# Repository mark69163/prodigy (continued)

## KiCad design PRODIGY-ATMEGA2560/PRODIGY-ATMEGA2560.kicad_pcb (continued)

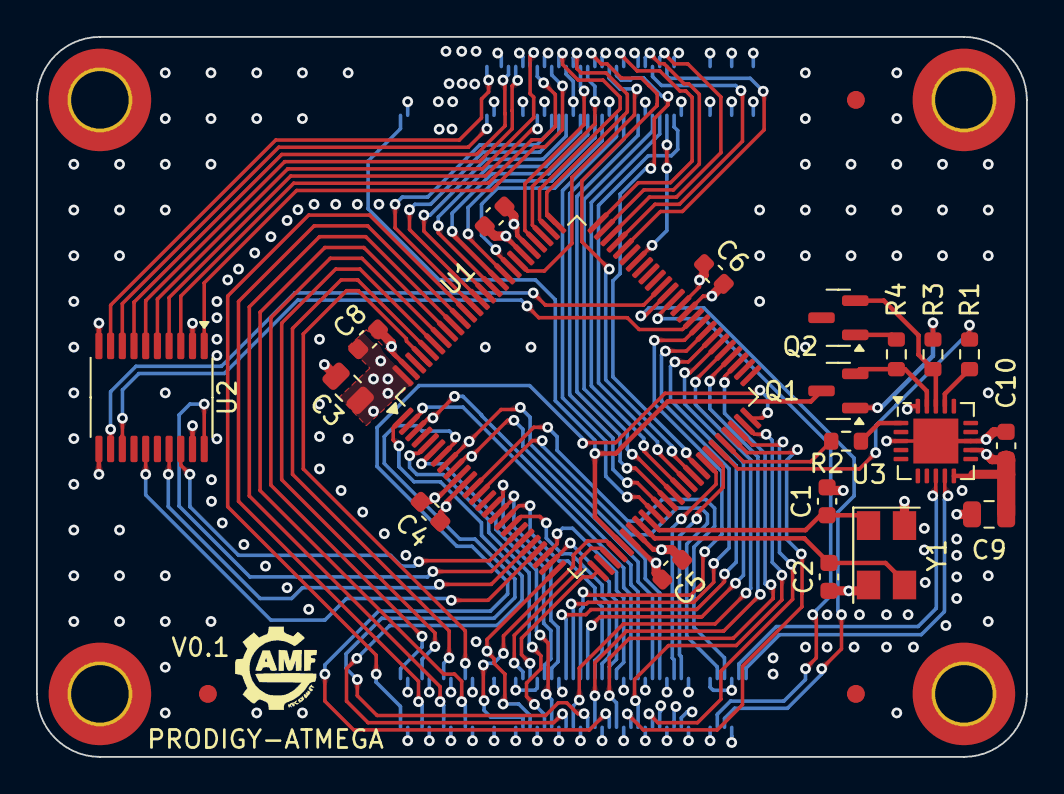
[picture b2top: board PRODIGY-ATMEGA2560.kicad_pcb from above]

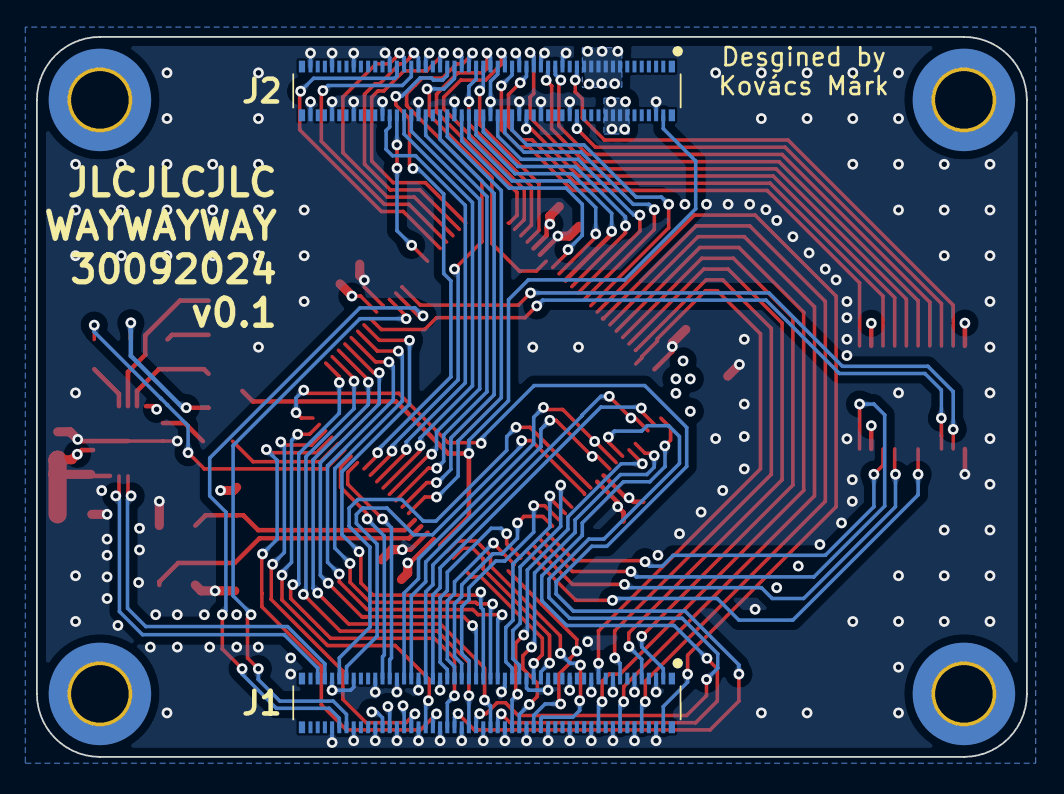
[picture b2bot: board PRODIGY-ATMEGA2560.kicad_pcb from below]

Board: 4 copper layers, 55.0 x 40.0 mm, 29 parts (2 on the bottom side), 99 nets.

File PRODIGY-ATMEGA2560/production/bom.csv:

Designator,Footprint,Quantity,Value,LCSC Part #
"C1, C2",0603,2,4.7pF,
"C10, C4, C5, C6, C7, C8",0603,6,100nF,
"C3, C9",0805,2,10uF,
"FID1, FID2, FID3",Fiducial_1mm_Mask3mm,3,Fiducial,
"H1, H2, H3, H4",MountingHole_3.2mm_M3_ISO7380_Pad_TopBottom,4,MountingHole,
"J1, J2",DF40C100DP04V51,2,DF40C-100DP-04V-51 ,
"Q1, Q2",SOT-23,2,BC850,
"R1, R2",0603,2,0R,
"R3, R4",0603,2,10k,
U1,TQFP-100_14x14mm_P0.5mm,1,ATmega2560-8A,
U2,TSSOP-20_4.4x6.5mm_P0.65mm,1,TXS0108EPW,
U3,QFN-20-1EP_4x4mm_P0.5mm_EP2.5x2.5mm,1,FT231XQ,
Y1,Crystal_SMD_5032-4Pin_5.0x3.2mm,1,8MHz,

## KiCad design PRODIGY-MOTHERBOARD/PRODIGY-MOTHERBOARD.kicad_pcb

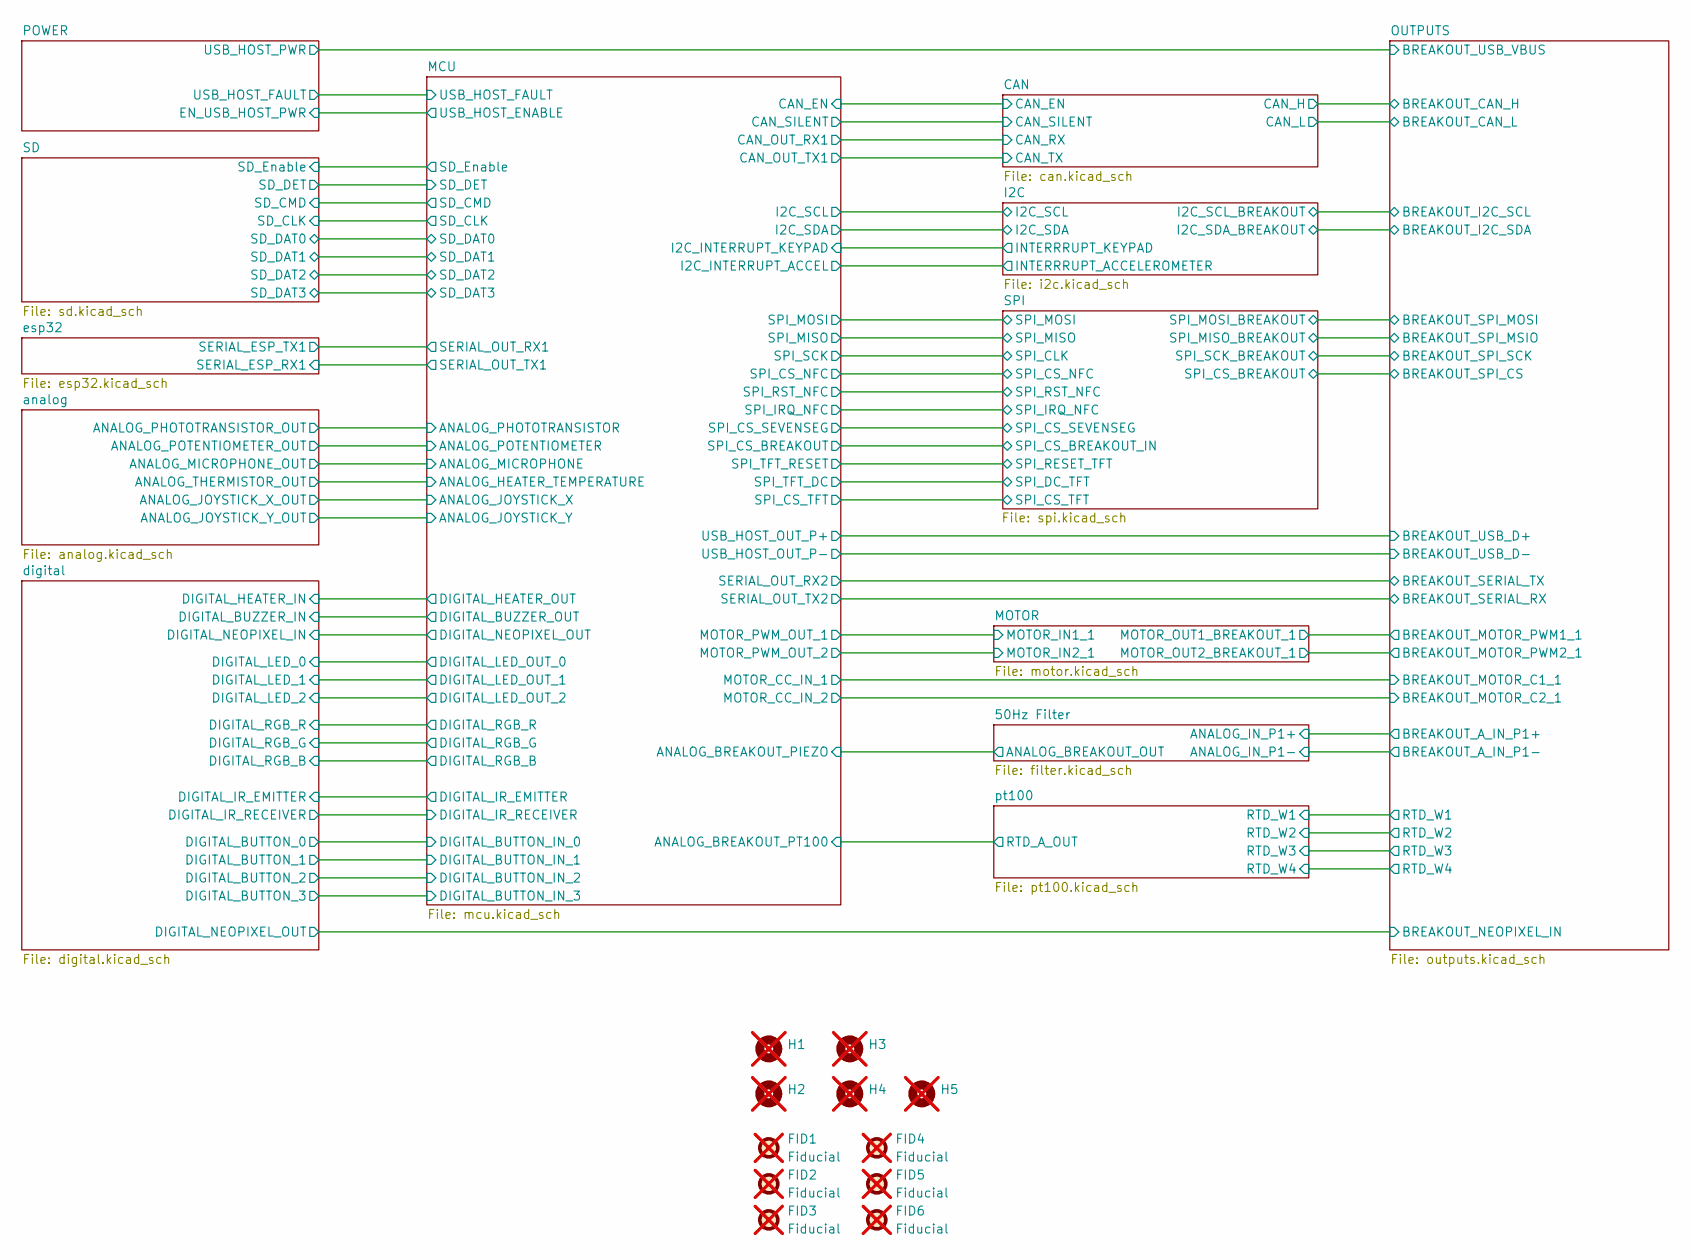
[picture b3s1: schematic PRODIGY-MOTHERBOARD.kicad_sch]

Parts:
FID1, FID2, FID3, FID4, FID5, FID6: Fiducial; Fiducial_1mm_Mask3mm; not fitted
H1, H2, H3, H4, H5: MountingHole; MountingHole_3.2mm_M3_ISO7380_Pad_TopBottom; not fitted

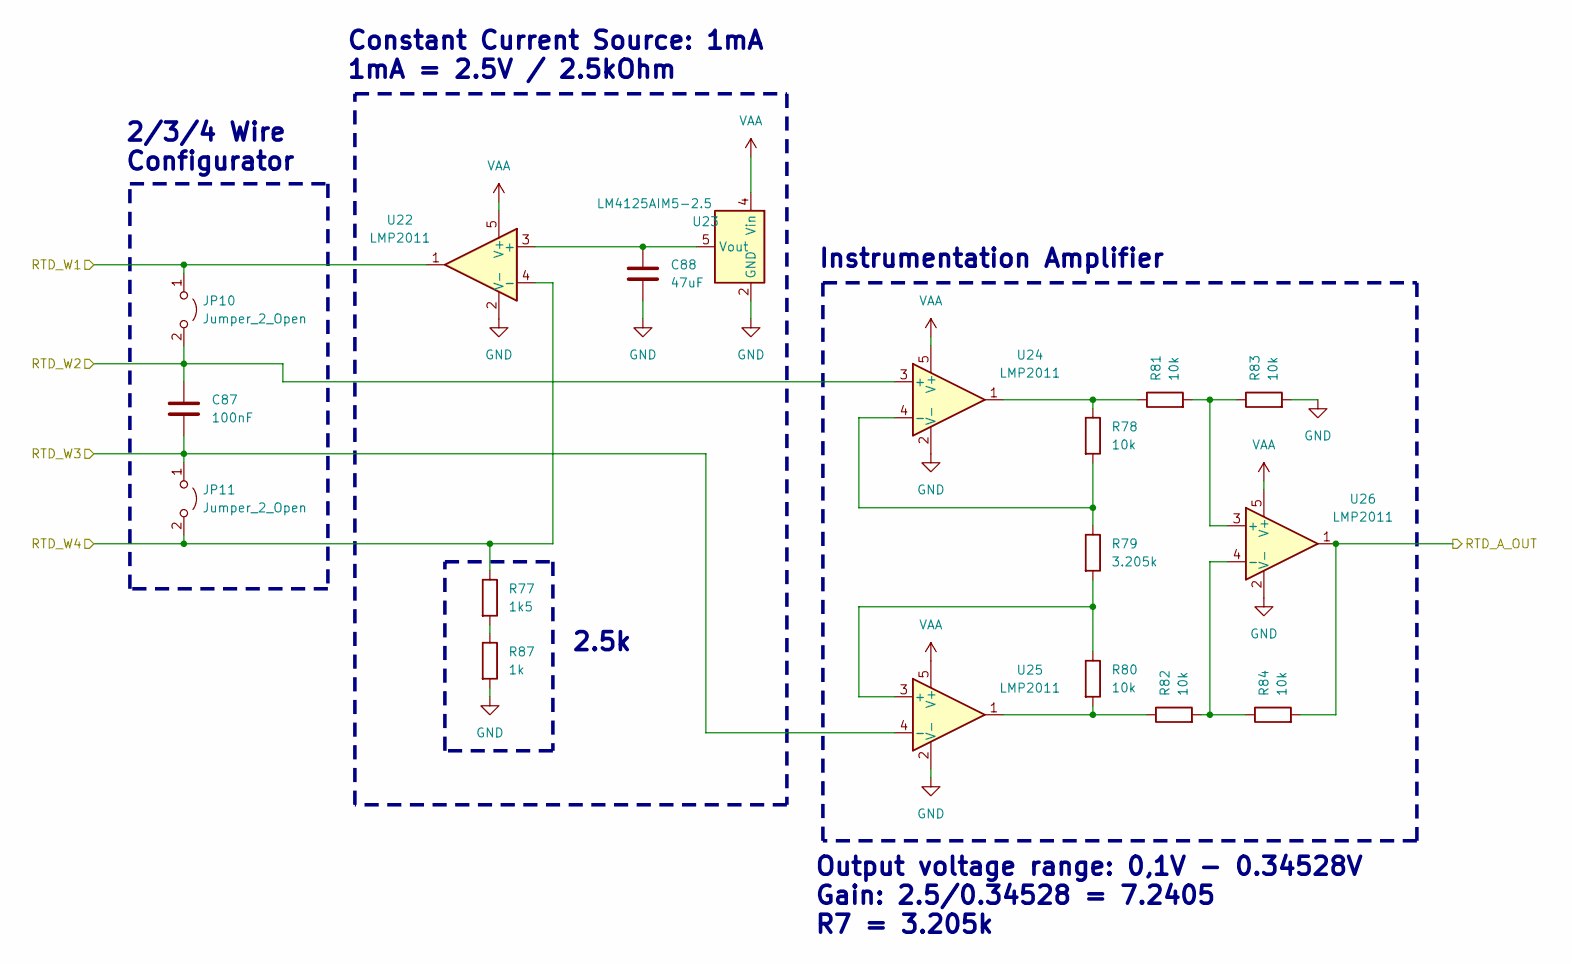
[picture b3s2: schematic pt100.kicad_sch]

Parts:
C87: 100nF; C_0603_1608Metric
C88: 47uF; C_1210_3225Metric
JP10, JP11: Jumper_2_Open; PinHeader_1x02_P2.54mm_Vertical
R77: 1k5; R_0603_1608Metric
R78, R80, R81, R82, R83, R84: 10k; R_0603_1608Metric
R79: 3.205k; R_0603_1608Metric
R87: 1k; R_0603_1608Metric
U22, U24, U25, U26: LMP2011; TSOT-23-5; MOUSER 926-LMP2011MFX/NOPB
U23: LM4125AIM5-2.5; SOT-23-5; MOUSER 926-LM4125IM525NOPB

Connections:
/MCU/ANALOG_BREAKOUT_PT100: R84.2, U26.1; also elsewhere on the board
/OUTPUTS/RTD_W1: JP10.1 (A), U22.1; also elsewhere on the board
/OUTPUTS/RTD_W2: C87.1, JP10.2 (B), U24.3 (+); also elsewhere on the board
/OUTPUTS/RTD_W3: C87.2, JP11.1 (A), U25.4 (-); also elsewhere on the board
/OUTPUTS/RTD_W4: JP11.2 (B), R77.1, U22.4 (-); also elsewhere on the board
GND: C88.2, R83.2, R87.2, U22.2 (V-), U23.2 (GND), U24.2 (V-), U25.2 (V-), U26.2 (V-); also elsewhere on the board
unnamed: R77.2, R87.1
unnamed: R78.1, R81.1, U24.1
unnamed: R80.2, R82.1, U25.1
unnamed: C88.1, U22.3 (+), U23.5 (Vout)
unnamed: R78.2, R79.1, U24.4 (-)
unnamed: R79.2, R80.1, U25.3 (+)
unnamed: R81.2, R83.1, U26.3 (+)
unnamed: R82.2, R84.1, U26.4 (-)
VAA: U22.5 (V+), U23.4 (Vin), U24.5 (V+), U25.5 (V+), U26.5 (V+); also elsewhere on the board

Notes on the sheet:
Output voltage range: 0,1V - 0.34528V Gain: 2.5/0.34528 = 7.2405 R7 = 3.205k
Constant Current Source: 1mA 1mA = 2.5V / 2.5kOhm
2/3/4 Wire Configurator
Instrumentation Amplifier
2.5k

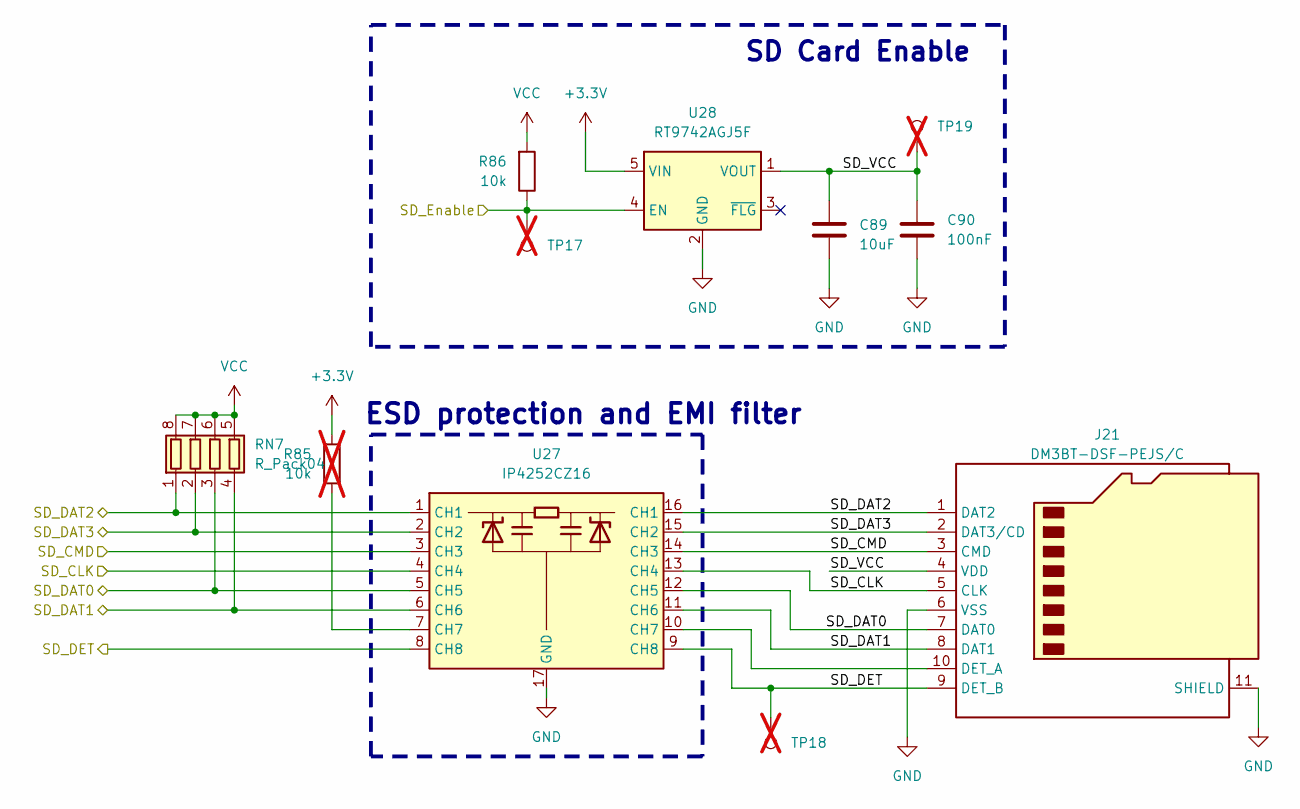
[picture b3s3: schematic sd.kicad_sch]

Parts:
C89: 10uF; C_0805_2012Metric
C90: 100nF; C_0603_1608Metric
J21: DM3BT-DSF-PEJS/C; microSD_HC_Hirose_DM3BT-DSF-PEJS
R85: 10k; R_0603_1608Metric; not fitted
R86: 10k; R_0603_1608Metric
RN7: R_Pack04; R_Array_Convex_4x0603
TP17, TP18, TP19: TestPoint_Pad_D3.0mm; not fitted
U27: IP4252CZ16; Nexperia_HUSON-16_USON-16-1EP_1.35x3.3mm_P0.4mm_EP0.4x2.8mm; MOUSER 771-IP4252CZ168TTL1
U28: RT9742AGJ5F; TSOT-23-5; MOUSER 835-RT9742AGJ5F

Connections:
+3.3V: R85.2, U28.5 (VIN); also elsewhere on the board
/MCU/SD_Enable: R86.1, TP17.1, U28.4 (EN); also elsewhere on the board
/SD/SD_CLK: J21.5 (CLK), U27.4 (CH4), U27.13 (CH4); also elsewhere on the board
/SD/SD_CMD: J21.3 (CMD), U27.3 (CH3), U27.14 (CH3); also elsewhere on the board
/SD/SD_DAT0: J21.7 (DAT0), RN7.3 (R3.1), U27.5 (CH5), U27.12 (CH5); also elsewhere on the board
/SD/SD_DAT1: J21.8 (DAT1), RN7.4 (R4.1), U27.6 (CH6), U27.11 (CH6); also elsewhere on the board
/SD/SD_DAT2: J21.1 (DAT2), RN7.1 (R1.1), U27.1 (CH1), U27.16 (CH1); also elsewhere on the board
/SD/SD_DAT3: J21.2 (DAT3/CD), RN7.2 (R2.1), U27.2 (CH2), U27.15 (CH2); also elsewhere on the board
/SD/SD_DET: J21.9 (DET_B), TP18.1, U27.8 (CH8), U27.9 (CH8); also elsewhere on the board
/SD/SD_VCC: C89.1, C90.1, J21.4 (VDD), TP19.1, U28.1 (VOUT)
GND: C89.2, C90.2, J21.6 (VSS), J21.11 (SHIELD), U27.17 (GND), U28.2 (GND); also elsewhere on the board
unnamed: J21.10 (DET_A), U27.10 (CH7)
unnamed: R85.1, U27.7 (CH7)
VCC: R86.2, RN7.5 (R4.2), RN7.6 (R3.2), RN7.7 (R2.2), RN7.8 (R1.2); also elsewhere on the board

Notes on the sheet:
SD Card Enable
ESD protection and EMI filter

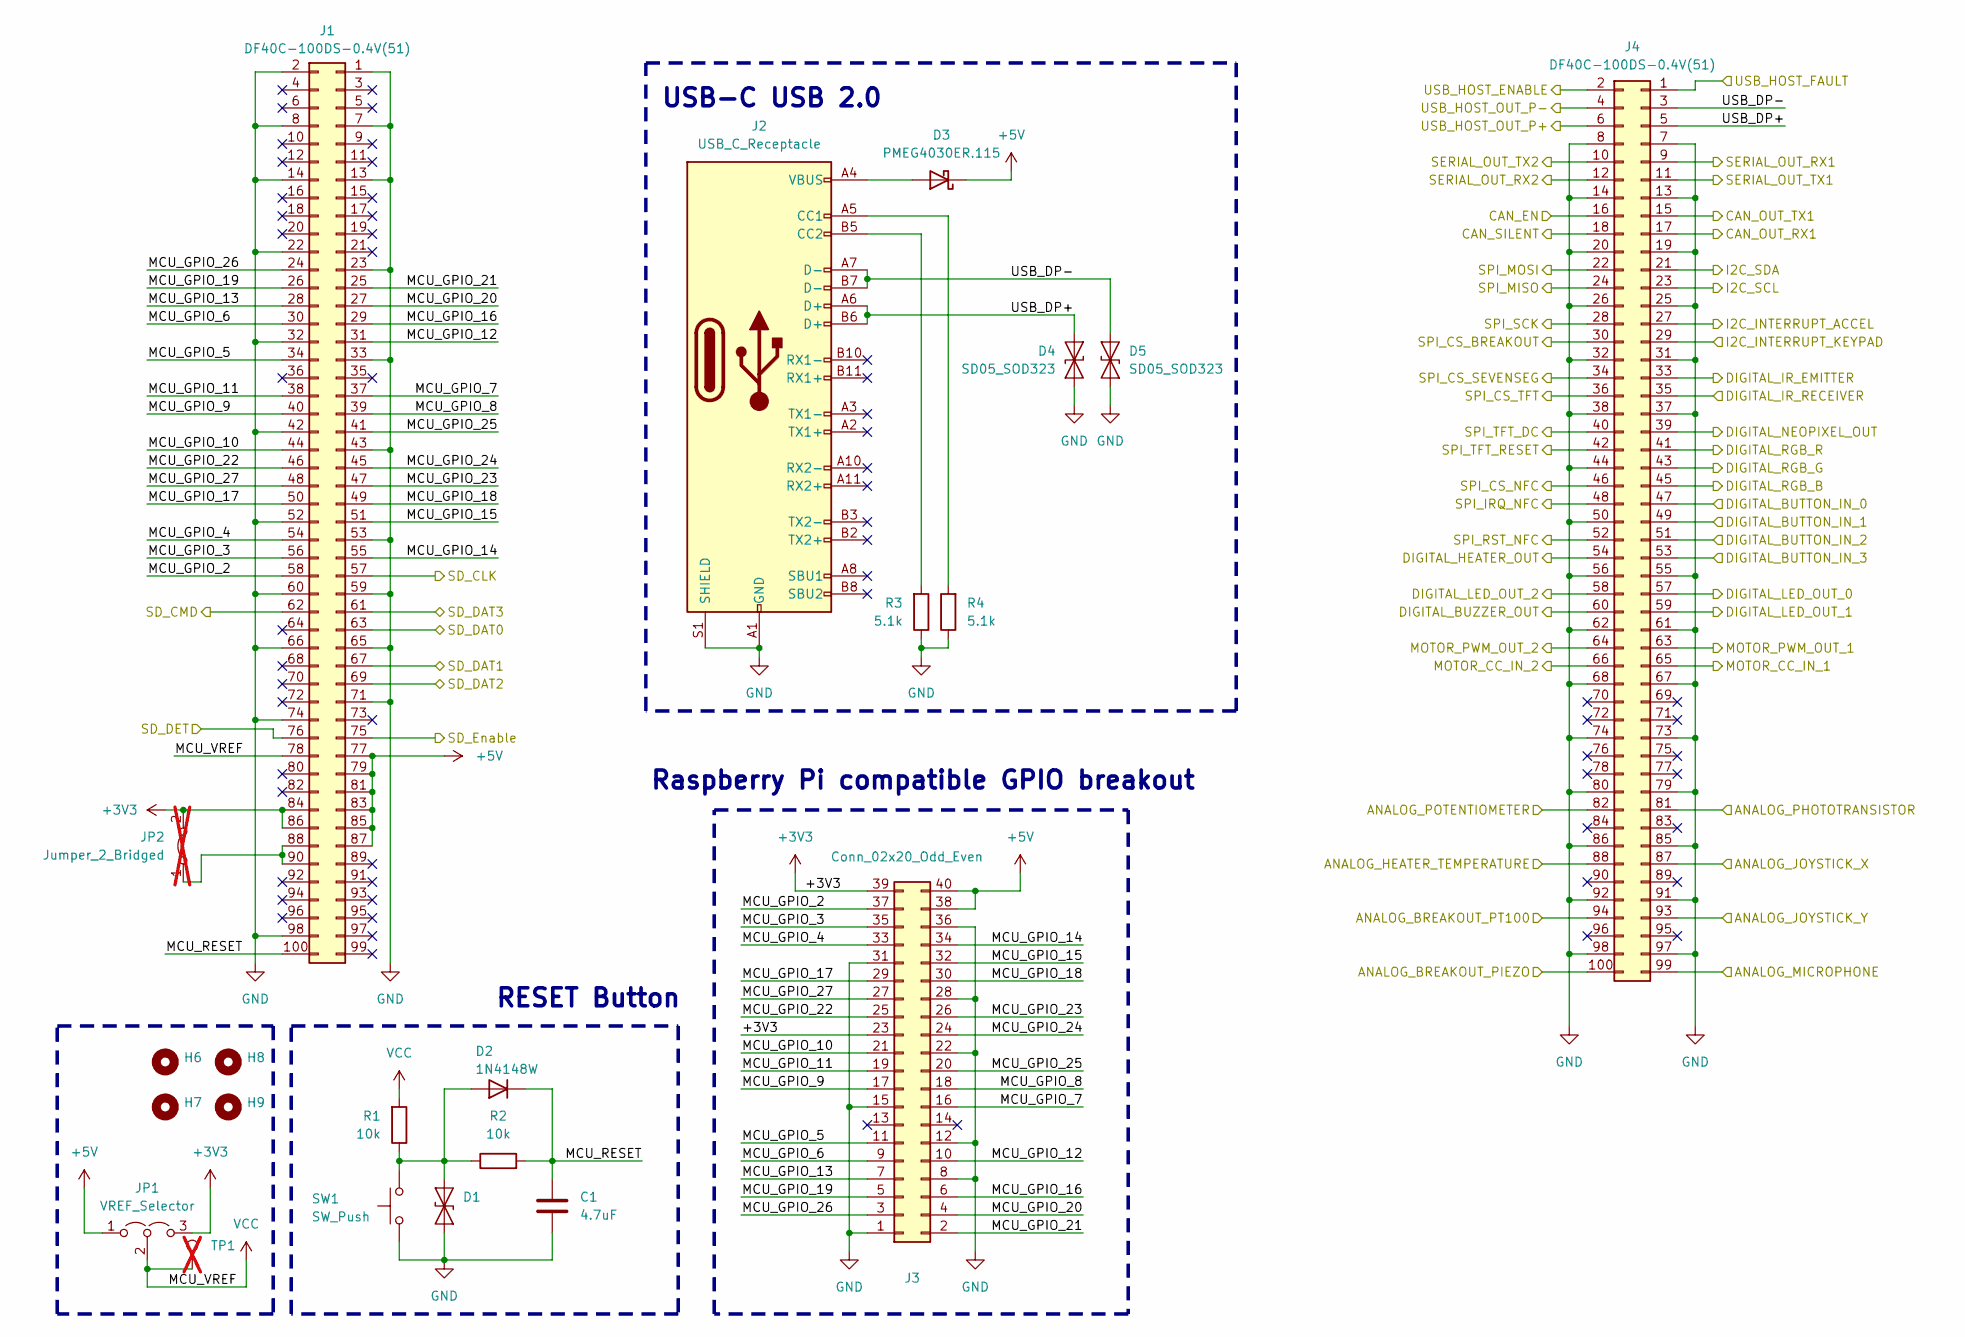
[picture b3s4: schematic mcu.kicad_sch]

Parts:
C1: 4.7uF; C_0805_2012Metric
D1, D4, D5: SD05_SOD323; D_SOD-323
D2: 1N4148W; D_SOD-323
D3: PMEG4030ER.115; Nexperia_CFP3_SOD-123W
H6, H7, H8, H9: MountingHole; MountingHole_4.3mm_M4_ISO14580_Pad
J1, J4: DF40C-100DS-0.4V(51); HIROSE_DF40C-100DS-0.4V_51_
J2: USB_C_Receptacle; USB_C_Receptacle_XKB_U262-16XN-4BVC11; MOUSER 523-GSB1C411111DS1HR
J3: Conn_02x20_Odd_Even; IDC-Header_2x20_P2.54mm_Horizontal
JP1: VREF_Selector; PinHeader_1x03_P2.54mm_Vertical
JP2: Jumper_2_Bridged; SolderJumper-2_P1.3mm_Open_Pad1.0x1.5mm; not fitted
R1, R2: 10k; R_0603_1608Metric
R3, R4: 5.1k; R_0603_1608Metric
SW1: SW_Push; SW_Push_1P1T_NO_CK_KMR2
TP1: TestPoint_Pad_D3.0mm; not fitted

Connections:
+3V3: J1.84, J1.86, J3.23, J3.39, JP1.3 (B), JP2.2 (B); also elsewhere on the board
+5V: D3.1 (K), J1.77, J1.79, J1.81, J1.83, J1.85, J1.87, J3.38, J3.40, JP1.1 (A); also elsewhere on the board
/50Hz Filter/ANALOG_BREAKOUT_OUT: J4.100; also elsewhere on the board
/CAN/CAN_EN: J4.16; also elsewhere on the board
/CAN/CAN_RX: J4.17; also elsewhere on the board
/CAN/CAN_SILENT: J4.18; also elsewhere on the board
/CAN/CAN_TX: J4.15; also elsewhere on the board
/I2C/I2C_SCL_3V3: J4.23; also elsewhere on the board
/I2C/I2C_SDA_3V3: J4.21; also elsewhere on the board
/I2C/INTERRRUPT_ACCELEROMETER: J4.27; also elsewhere on the board
/I2C/INTERRRUPT_KEYPAD: J4.29; also elsewhere on the board
/MCU/ANALOG_BREAKOUT_PT100: J4.94; also elsewhere on the board
/MCU/ANALOG_HEATER_TEMPERATURE: J4.88; also elsewhere on the board
/MCU/ANALOG_JOYSTICK_X: J4.87; also elsewhere on the board
/MCU/ANALOG_JOYSTICK_Y: J4.93; also elsewhere on the board
/MCU/ANALOG_MICROPHONE: J4.99; also elsewhere on the board
/MCU/ANALOG_PHOTOTRANSISTOR: J4.81; also elsewhere on the board
/MCU/ANALOG_POTENTIOMETER: J4.82; also elsewhere on the board
/MCU/DIGITAL_BUTTON_IN_0: J4.47; also elsewhere on the board
/MCU/DIGITAL_BUTTON_IN_1: J4.49; also elsewhere on the board
/MCU/DIGITAL_BUTTON_IN_2: J4.51; also elsewhere on the board
/MCU/DIGITAL_BUTTON_IN_3: J4.53; also elsewhere on the board
/MCU/DIGITAL_BUZZER_OUT: J4.60; also elsewhere on the board
/MCU/DIGITAL_HEATER_OUT: J4.54; also elsewhere on the board
/MCU/DIGITAL_IR_EMITTER: J4.33; also elsewhere on the board
/MCU/DIGITAL_IR_RECEIVER: J4.35; also elsewhere on the board
/MCU/DIGITAL_LED_OUT_0: J4.57; also elsewhere on the board
/MCU/DIGITAL_LED_OUT_1: J4.59; also elsewhere on the board
/MCU/DIGITAL_LED_OUT_2: J4.58; also elsewhere on the board
/MCU/DIGITAL_NEOPIXEL_OUT: J4.39; also elsewhere on the board
/MCU/DIGITAL_RGB_B: J4.45; also elsewhere on the board
/MCU/DIGITAL_RGB_G: J4.43; also elsewhere on the board
/MCU/DIGITAL_RGB_R: J4.41; also elsewhere on the board
/MCU/MCU_GPIO_2: J1.58, J3.37
/MCU/MCU_GPIO_3: J1.56, J3.35
/MCU/MCU_GPIO_4: J1.54, J3.33
/MCU/MCU_GPIO_5: J1.34, J3.11
/MCU/MCU_GPIO_6: J1.30, J3.9
/MCU/MCU_GPIO_7: J1.37, J3.16
/MCU/MCU_GPIO_8: J1.39, J3.18
/MCU/MCU_GPIO_9: J1.40, J3.17
/MCU/MCU_GPIO_10: J1.44, J3.21
/MCU/MCU_GPIO_11: J1.38, J3.19
/MCU/MCU_GPIO_12: J1.31, J3.10
/MCU/MCU_GPIO_13: J1.28, J3.7
/MCU/MCU_GPIO_14: J1.55, J3.34
/MCU/MCU_GPIO_15: J1.51, J3.32
/MCU/MCU_GPIO_16: J1.29, J3.6
/MCU/MCU_GPIO_17: J1.50, J3.29
/MCU/MCU_GPIO_18: J1.49, J3.30
/MCU/MCU_GPIO_19: J1.26, J3.5
/MCU/MCU_GPIO_20: J1.27, J3.4
/MCU/MCU_GPIO_21: J1.25, J3.2
/MCU/MCU_GPIO_22: J1.46, J3.25
/MCU/MCU_GPIO_23: J1.47, J3.26
/MCU/MCU_GPIO_24: J1.45, J3.24
/MCU/MCU_GPIO_25: J1.41, J3.20
/MCU/MCU_GPIO_26: J1.24, J3.3
/MCU/MCU_GPIO_27: J1.48, J3.27
/MCU/MCU_RESET: C1.1, D2.1 (K), J1.100, R2.2
/MCU/MOTOR_CC_IN_1: J4.65; also elsewhere on the board
/MCU/MOTOR_CC_IN_2: J4.66; also elsewhere on the board
/MCU/MOTOR_PWM_OUT_1: J4.63; also elsewhere on the board
/MCU/MOTOR_PWM_OUT_2: J4.64; also elsewhere on the board
/MCU/SD_Enable: J1.75; also elsewhere on the board
/MCU/SERIAL_OUT_RX1: J4.9; also elsewhere on the board
/MCU/SERIAL_OUT_RX2: J4.12; also elsewhere on the board
/MCU/SERIAL_OUT_TX1: J4.11; also elsewhere on the board
/MCU/SERIAL_OUT_TX2: J4.10; also elsewhere on the board
/MCU/SPI_CS_BREAKOUT: J4.30; also elsewhere on the board
/MCU/SPI_CS_NFC: J4.46; also elsewhere on the board
/MCU/SPI_CS_SEVENSEG: J4.34; also elsewhere on the board
/MCU/SPI_CS_TFT: J4.36; also elsewhere on the board
/MCU/SPI_IRQ_NFC: J4.48; also elsewhere on the board
/MCU/SPI_MISO: J4.24; also elsewhere on the board
/MCU/SPI_MOSI: J4.22; also elsewhere on the board
/MCU/SPI_RST_NFC: J4.52; also elsewhere on the board
/MCU/SPI_SCK: J4.28; also elsewhere on the board
/MCU/SPI_TFT_DC: J4.40; also elsewhere on the board
/MCU/SPI_TFT_RESET: J4.42; also elsewhere on the board
/MCU/USB_DP+: D4.2 (A2), J2.A6 (D+), J2.B6 (D+), J4.5
/MCU/USB_DP-: D5.2 (A2), J2.A7 (D-), J2.B7 (D-), J4.3
/MCU/USB_HOST_ENABLE: J4.2; also elsewhere on the board
/MCU/USB_HOST_FAULT: J4.1; also elsewhere on the board
/MCU/USB_HOST_OUT_P+: J4.6; also elsewhere on the board
/MCU/USB_HOST_OUT_P-: J4.4; also elsewhere on the board
/SD/SD_CLK: J1.57; also elsewhere on the board
/SD/SD_CMD: J1.62; also elsewhere on the board
/SD/SD_DAT0: J1.63; also elsewhere on the board
/SD/SD_DAT1: J1.67; also elsewhere on the board
/SD/SD_DAT2: J1.69; also elsewhere on the board
/SD/SD_DAT3: J1.61; also elsewhere on the board
/SD/SD_DET: J1.76; also elsewhere on the board
GND: C1.2, D1.1 (A1), D4.1 (A1), D5.1 (A1), J1.1, J1.2, J1.7, J1.8, J1.13, J1.14, J1.22, J1.23, J1.32, J1.33, J1.42, J1.43, J1.52, J1.53, J1.59, J1.60, J1.65, J1.66, J1.71, J1.74, J1.98, J2.A1 (GND), J2.A12 (GND), J2.B1 (GND), J2.B12 (GND), J2.S1 (SHIELD), J3.1, J3.8, J3.12, J3.15, J3.22, J3.28, J3.31, J3.36, J4.7, J4.8, J4.13, J4.14, J4.19, J4.20, J4.25, J4.26, J4.31, J4.32, J4.37, J4.38, J4.44, J4.50, J4.55, J4.56, J4.61, J4.62, J4.67, J4.68, J4.73, J4.74, J4.79, J4.80, J4.85, J4.86, J4.91, J4.92, J4.97, J4.98, R3.1, R4.1, SW1.1; also elsewhere on the board
unnamed: D1.2 (A2), D2.2 (A), R1.1, R2.1, SW1.2
unnamed: D3.2 (A), J2.A4 (VBUS), J2.A9 (VBUS), J2.B4 (VBUS), J2.B9 (VBUS)
unnamed: J2.A5 (CC1), R4.2
unnamed: J2.B5 (CC2), R3.2
unnamed: J1.88, J1.90, JP2.1 (A)
VCC: J1.78, JP1.2 (C), R1.2, TP1.1; also elsewhere on the board

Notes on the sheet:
Raspberry Pi compatible GPIO breakout
USB-C USB 2.0
RESET Button

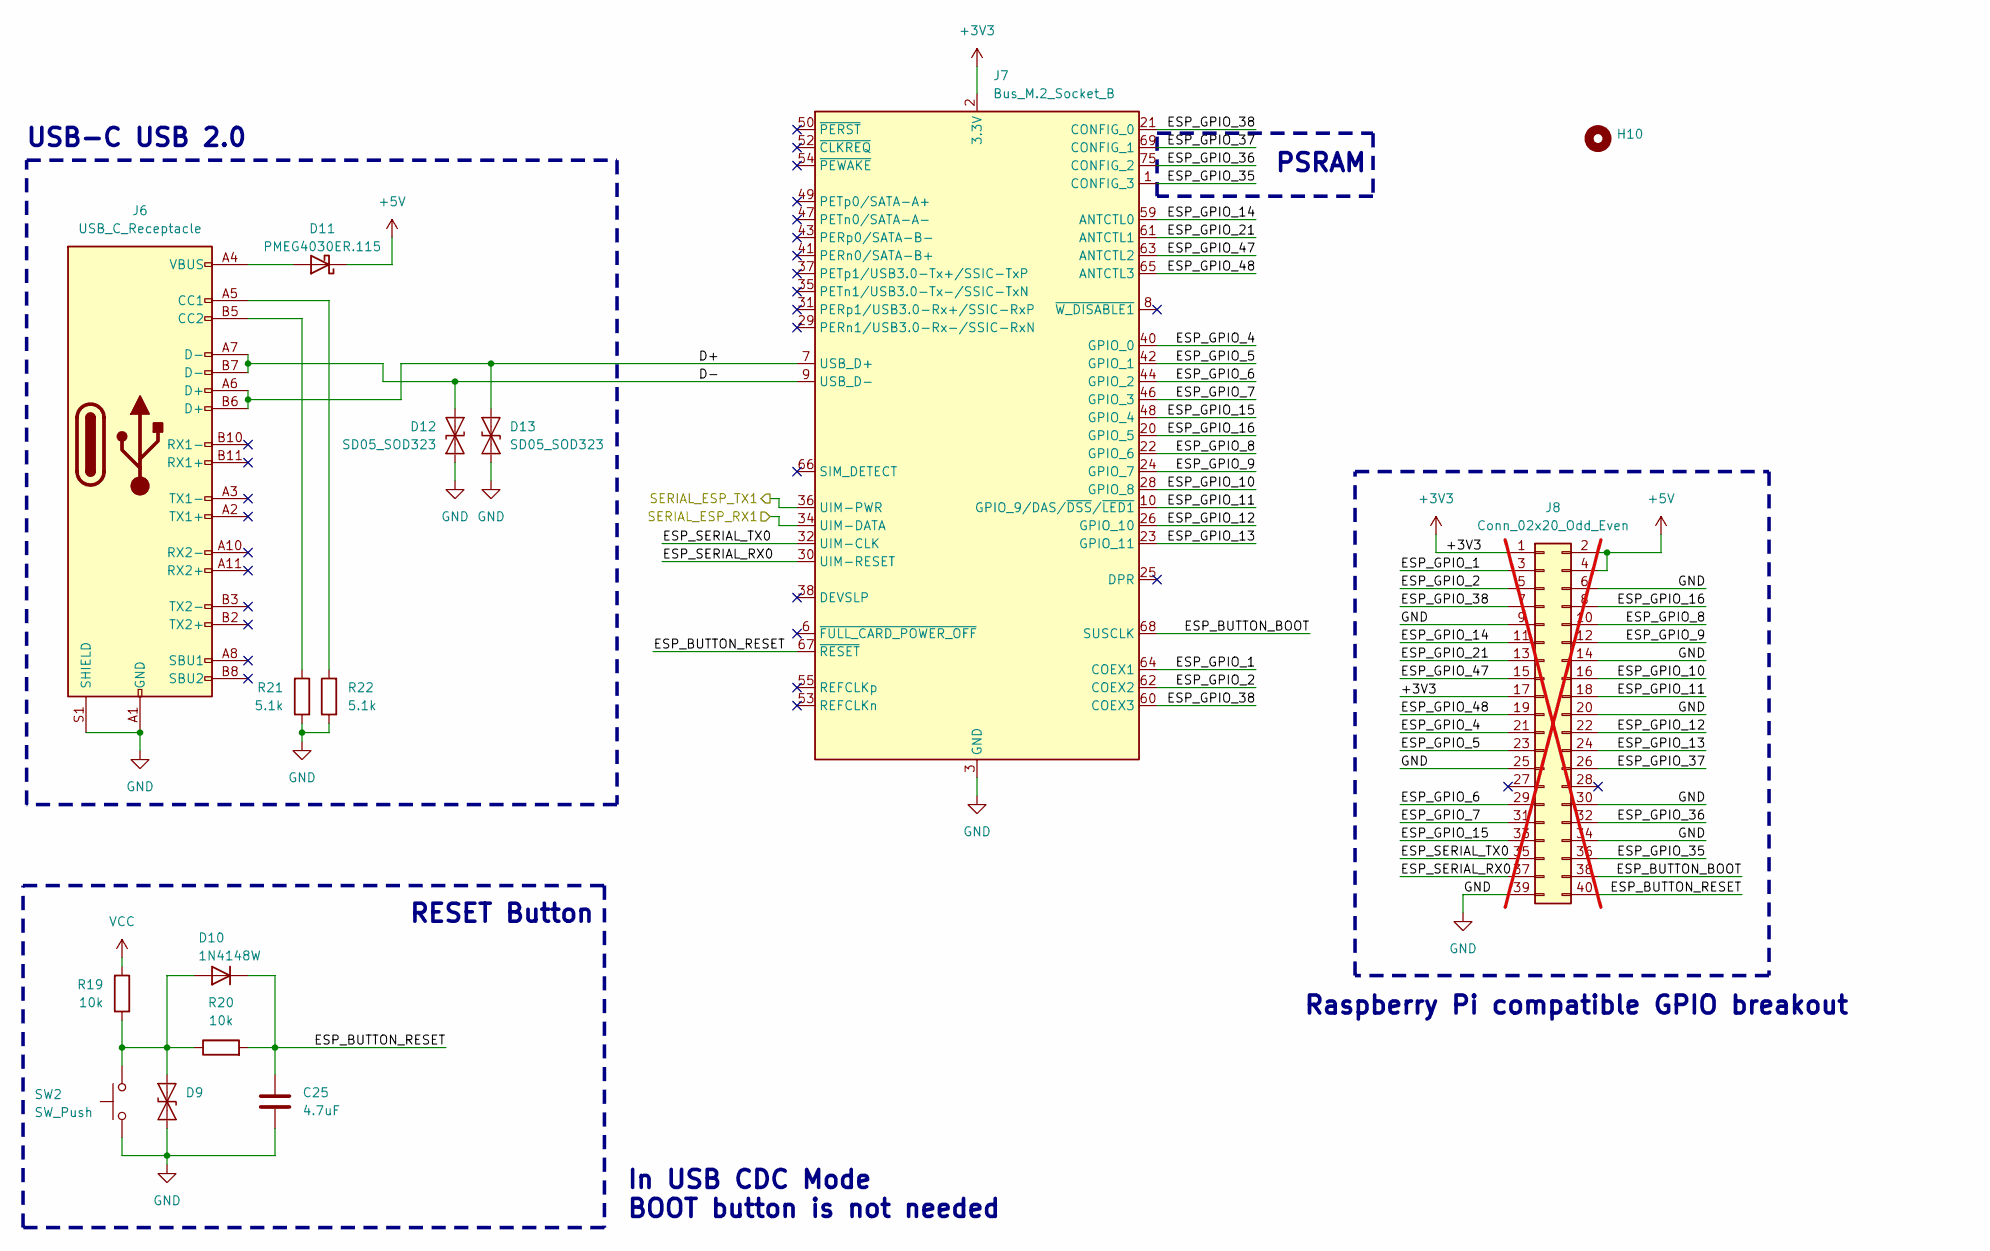
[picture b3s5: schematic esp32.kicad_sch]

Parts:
C25: 4.7uF; C_0805_2012Metric
D9, D12, D13: SD05_SOD323; D_SOD-323
D10: 1N4148W; D_SOD-323
D11: PMEG4030ER.115; Nexperia_CFP3_SOD-123W
H10: MountingHole; MountingHole_4.3mm_M4_ISO14580_Pad; MOUSER 710-9774040360R
J6: USB_C_Receptacle; USB_C_Receptacle_XKB_U262-16XN-4BVC11; MOUSER 523-GSB1C411111DS1HR
J7: Bus_M.2_Socket_B; 121992304
J8: Conn_02x20_Odd_Even; IDC-Header_2x20_P2.54mm_Horizontal; not fitted
R19, R20: 10k; R_0603_1608Metric
R21, R22: 5.1k; R_0603_1608Metric
SW2: SW_Push; SW_Push_1P1T_NO_CK_KMR2

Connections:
+3V3: J7.2 (3.3V), J7.4 (3.3V), J7.70 (3.3V), J7.72 (3.3V), J7.74 (3.3V), J8.1, J8.17; also elsewhere on the board
+5V: D11.1 (K), J8.2, J8.4; also elsewhere on the board
/MCU/SERIAL_OUT_RX1: J7.36 (UIM-PWR); also elsewhere on the board
/MCU/SERIAL_OUT_TX1: J7.34 (UIM-DATA); also elsewhere on the board
/esp32/D+: D13.2 (A2), J6.A6 (D+), J6.B6 (D+), J7.7 (USB_D+)
/esp32/D-: D12.2 (A2), J6.A7 (D-), J6.B7 (D-), J7.9 (USB_D-)
/esp32/ESP_BUTTON_BOOT: J7.68 (SUSCLK), J8.38
/esp32/ESP_BUTTON_RESET: C25.1, D10.1 (K), J7.67 (~RESET), J8.40, R20.2
/esp32/ESP_GPIO_4: J7.40 (GPIO_0), J8.21
/esp32/ESP_GPIO_5: J7.42 (GPIO_1), J8.23
/esp32/ESP_GPIO_6: J7.44 (GPIO_2), J8.29
/esp32/ESP_GPIO_7: J7.46 (GPIO_3), J8.31
/esp32/ESP_GPIO_8: J7.22 (GPIO_6), J8.10
/esp32/ESP_GPIO_9: J7.24 (GPIO_7), J8.12
/esp32/ESP_GPIO_10: J7.28 (GPIO_8), J8.16
/esp32/ESP_GPIO_11: J7.10 (GPIO_9/DAS/~DSS/~LED1), J8.18
/esp32/ESP_GPIO_12: J7.26 (GPIO_10), J8.22
/esp32/ESP_GPIO_13: J7.23 (GPIO_11), J8.24
/esp32/ESP_GPIO_15: J7.48 (GPIO_4), J8.33
/esp32/ESP_GPIO_16: J7.20 (GPIO_5), J8.8
/esp32/ESP_GPIO_35: J7.1 (CONFIG_3), J8.36
/esp32/ESP_GPIO_36: J7.75 (CONFIG_2), J8.32
/esp32/ESP_GPIO_37: J7.69 (CONFIG_1), J8.26
/esp32/ESP_GPIO_38: J7.21 (CONFIG_0), J7.60 (COEX3), J8.7
/esp32/ESP_SERIAL_RX0: J7.30 (UIM-RESET), J8.37
/esp32/ESP_SERIAL_TX0: J7.32 (UIM-CLK), J8.35
GND: C25.2, D9.1 (A1), D12.1 (A1), D13.1 (A1), J6.A1 (GND), J6.A12 (GND), J6.B1 (GND), J6.B12 (GND), J6.S1 (SHIELD), J7.3 (GND), J7.5 (GND), J7.11 (GND), J7.27 (GND), J7.33 (GND), J7.39 (GND), J7.45 (GND), J7.51 (GND), J7.57 (GND), J7.71 (GND), J7.73 (GND), J8.6, J8.9, J8.14, J8.20, J8.25, J8.30, J8.34, J8.39, R21.1, R22.1, SW2.1; also elsewhere on the board
unnamed: D9.2 (A2), D10.2 (A), R19.1, R20.1, SW2.2
unnamed: D11.2 (A), J6.A4 (VBUS), J6.A9 (VBUS), J6.B4 (VBUS), J6.B9 (VBUS)
unnamed: J6.A5 (CC1), R22.2
unnamed: J6.B5 (CC2), R21.2
unnamed: J7.64 (COEX1), J8.3
unnamed: J7.62 (COEX2), J8.5
unnamed: J7.59 (ANTCTL0), J8.11
unnamed: J7.61 (ANTCTL1), J8.13
unnamed: J7.63 (ANTCTL2), J8.15
unnamed: J7.65 (ANTCTL3), J8.19
VCC: R19.2; also elsewhere on the board

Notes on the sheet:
In USB CDC Mode BOOT button is not needed
USB-C USB 2.0
RESET Button
Raspberry Pi compatible GPIO breakout
PSRAM

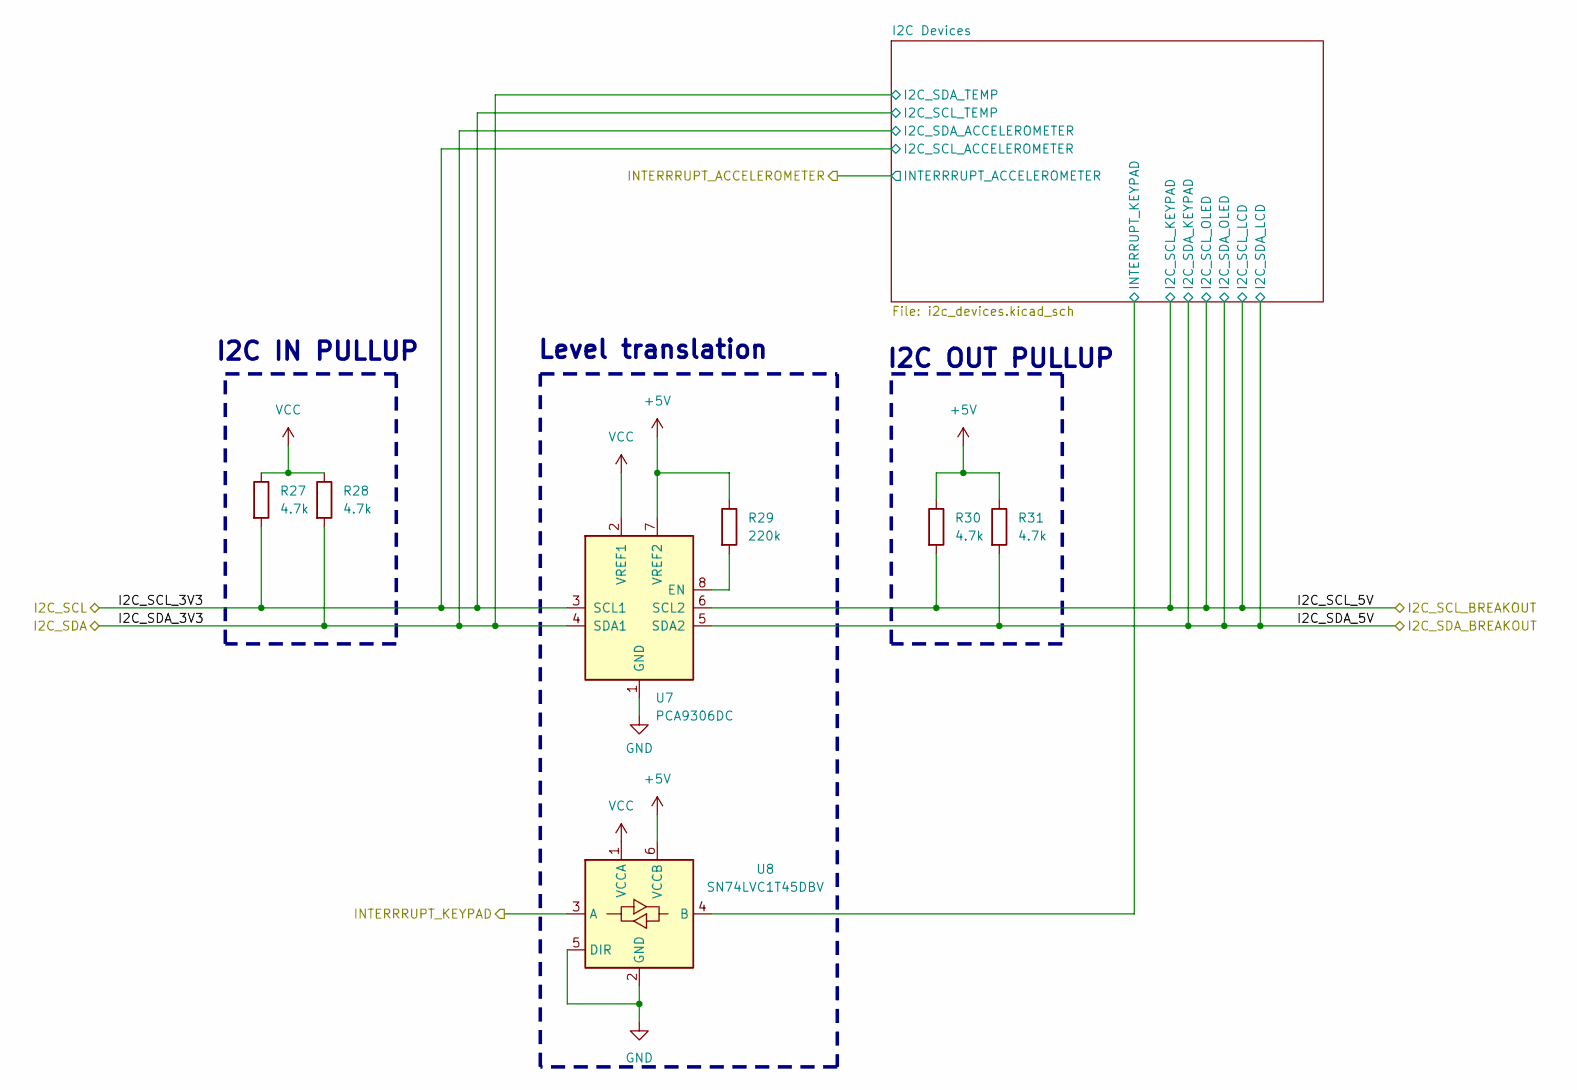
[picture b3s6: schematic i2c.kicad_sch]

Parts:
R27, R28, R30, R31: 4.7k; R_0603_1608Metric
R29: 220k; R_0603_1608Metric
U7: PCA9306DC; VSSOP-8_2.3x2mm_P0.5mm
U8: SN74LVC1T45DBV; SOT-23-6

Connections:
+5V: R29.1, R30.1, R31.1, U7.7 (VREF2), U8.6 (VCCB); also elsewhere on the board
/I2C/I2C Devices/INTERRUPT_KEYPAD: U8.4 (B); also elsewhere on the board
/I2C/I2C_SCL_3V3: R27.2, U7.3 (SCL1); also elsewhere on the board
/I2C/I2C_SCL_5V: R30.2, U7.6 (SCL2); also elsewhere on the board
/I2C/I2C_SDA_3V3: R28.2, U7.4 (SDA1); also elsewhere on the board
/I2C/I2C_SDA_5V: R31.2, U7.5 (SDA2); also elsewhere on the board
/I2C/INTERRRUPT_KEYPAD: U8.3 (A); also elsewhere on the board
GND: U7.1 (GND), U8.2 (GND), U8.5 (DIR); also elsewhere on the board
unnamed: R29.2, U7.8 (EN)
VCC: R27.1, R28.1, U7.2 (VREF1), U8.1 (VCCA); also elsewhere on the board

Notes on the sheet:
I2C IN PULLUP
Level translation
I2C OUT PULLUP

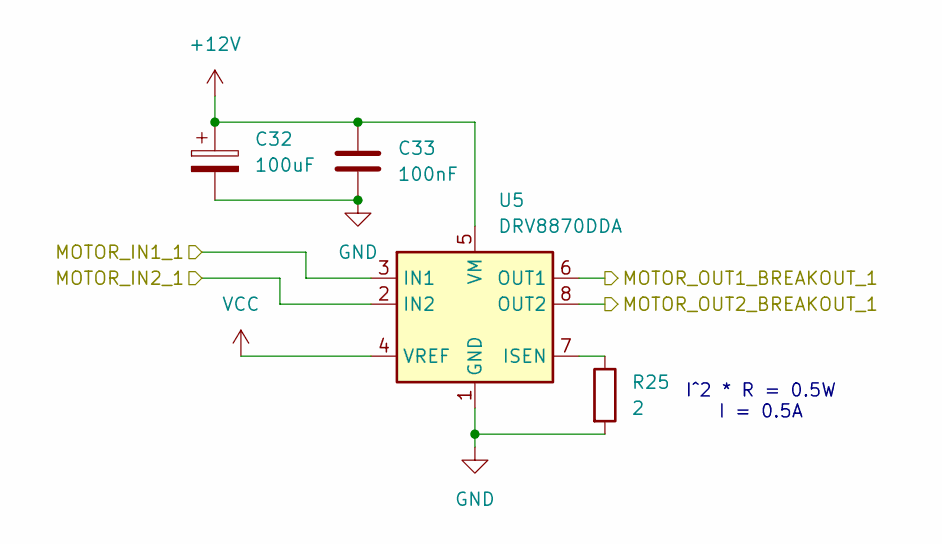
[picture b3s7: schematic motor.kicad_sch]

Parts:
C32: 100uF; CP_Elec_6.3x7.7
C33: 100nF; C_0603_1608Metric
R25: 2; R_2512_6332Metric
U5: DRV8870DDA; Texas_HTSOP-8-1EP_3.9x4.9mm_P1.27mm_EP2.95x4.9mm_Mask2.4x3.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

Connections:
+12V: C32.1, C33.1, U5.5 (VM); also elsewhere on the board
/MCU/MOTOR_PWM_OUT_1: U5.3 (IN1); also elsewhere on the board
/MCU/MOTOR_PWM_OUT_2: U5.2 (IN2); also elsewhere on the board
/MOTOR/MOTOR_OUT1_BREAKOUT_1: U5.6 (OUT1); also elsewhere on the board
/MOTOR/MOTOR_OUT2_BREAKOUT_1: U5.8 (OUT2); also elsewhere on the board
GND: C32.2, C33.2, R25.2, U5.1 (GND), U5.9 (GND); also elsewhere on the board
unnamed: R25.1, U5.7 (ISEN)
VCC: U5.4 (VREF); also elsewhere on the board

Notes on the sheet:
I^2 * R = 0.5W I = 0.5A
